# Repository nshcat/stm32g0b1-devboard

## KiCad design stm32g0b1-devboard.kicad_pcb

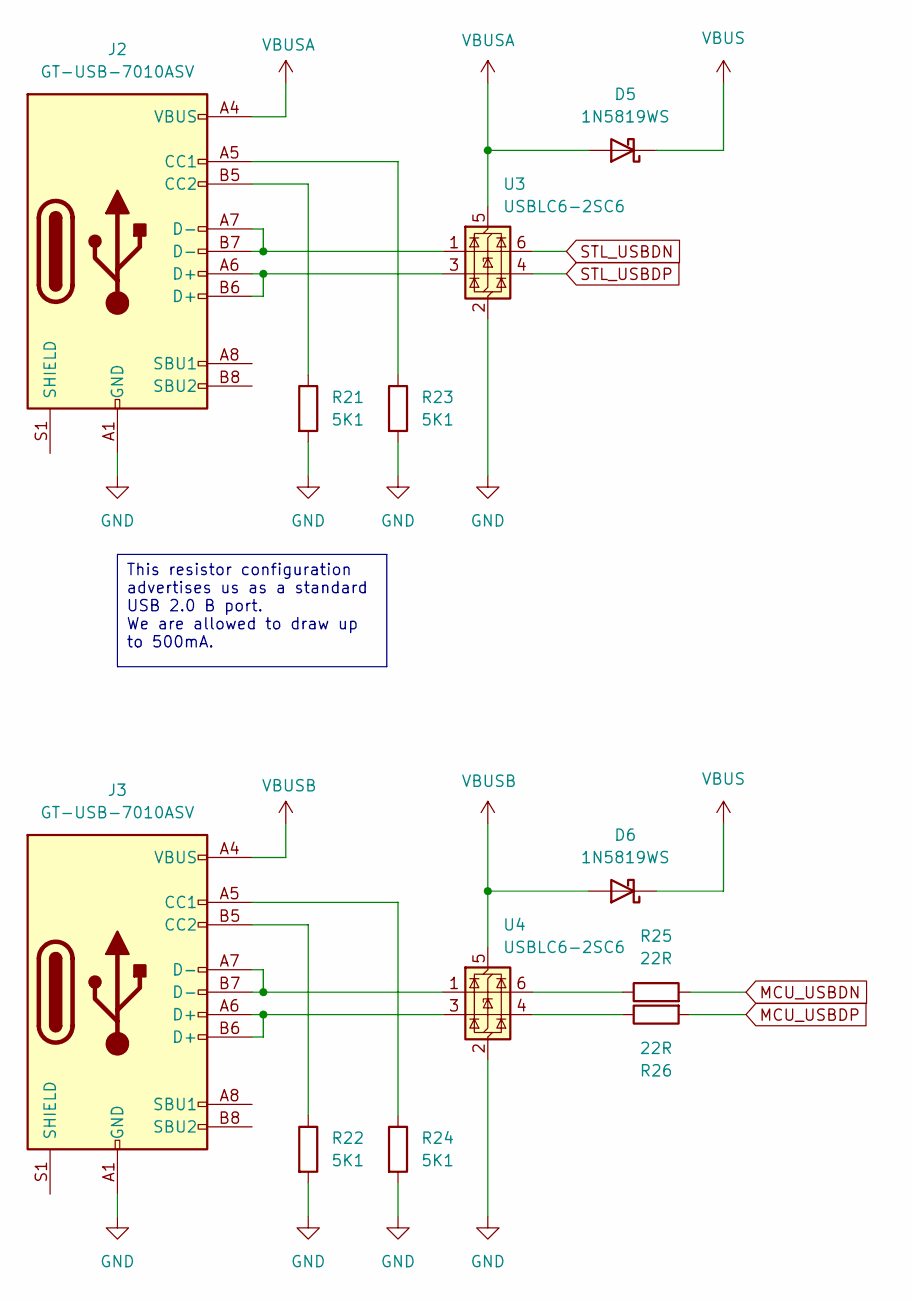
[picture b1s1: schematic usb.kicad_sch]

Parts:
D5, D6: 1N5819WS; D_SOD-323; LCSC Part # C191023
J2, J3: GT-USB-7010ASV; USB_C_Receptacle_G-Switch_GT-USB-7010ASV; LCSC Part # C2988369
R21, R22, R23, R24: 5K1; R_0402_1005Metric; LCSC Part # C25905
R25, R26: 22R; R_0402_1005Metric; LCSC Part # C25092
U3, U4: USBLC6-2SC6; SOT-23-6; LCSC Part # C2687116

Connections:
GND: J2.A1 (GND), J2.A12 (GND), J2.B1 (GND), J2.B12 (GND), J3.A1 (GND), J3.A12 (GND), J3.B1 (GND), J3.B12 (GND), R21.2, R22.2, R23.2, R24.2, U3.2 (GND), U4.2 (GND); also elsewhere on the board
MCU_USBDN: R25.2; also elsewhere on the board
MCU_USBDP: R26.2; also elsewhere on the board
unnamed: J2.A5 (CC1), R23.1
unnamed: J2.B5 (CC2), R21.1
unnamed: J2.A6 (D+), J2.B6 (D+), U3.3 (I/O2)
unnamed: J2.A7 (D-), J2.B7 (D-), U3.1 (I/O1)
unnamed: J3.A5 (CC1), R24.1
unnamed: J3.B5 (CC2), R22.1
unnamed: J3.A6 (D+), J3.B6 (D+), U4.3 (I/O2)
unnamed: J3.A7 (D-), J3.B7 (D-), U4.1 (I/O1)
unnamed: R25.1, U4.6 (I/O1)
unnamed: R26.1, U4.4 (I/O2)
STL_USBDN: U3.6 (I/O1); also elsewhere on the board
STL_USBDP: U3.4 (I/O2); also elsewhere on the board
VBUS: D5.1 (K), D6.1 (K); also elsewhere on the board
VBUSA: D5.2 (A), J2.A4 (VBUS), J2.A9 (VBUS), J2.B4 (VBUS), J2.B9 (VBUS), U3.5 (VBUS)
VBUSB: D6.2 (A), J3.A4 (VBUS), J3.A9 (VBUS), J3.B4 (VBUS), J3.B9 (VBUS), U4.5 (VBUS)

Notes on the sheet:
This resistor configuration advertises us as a standard USB 2.0 B port. We are allowed to draw up to 500mA.

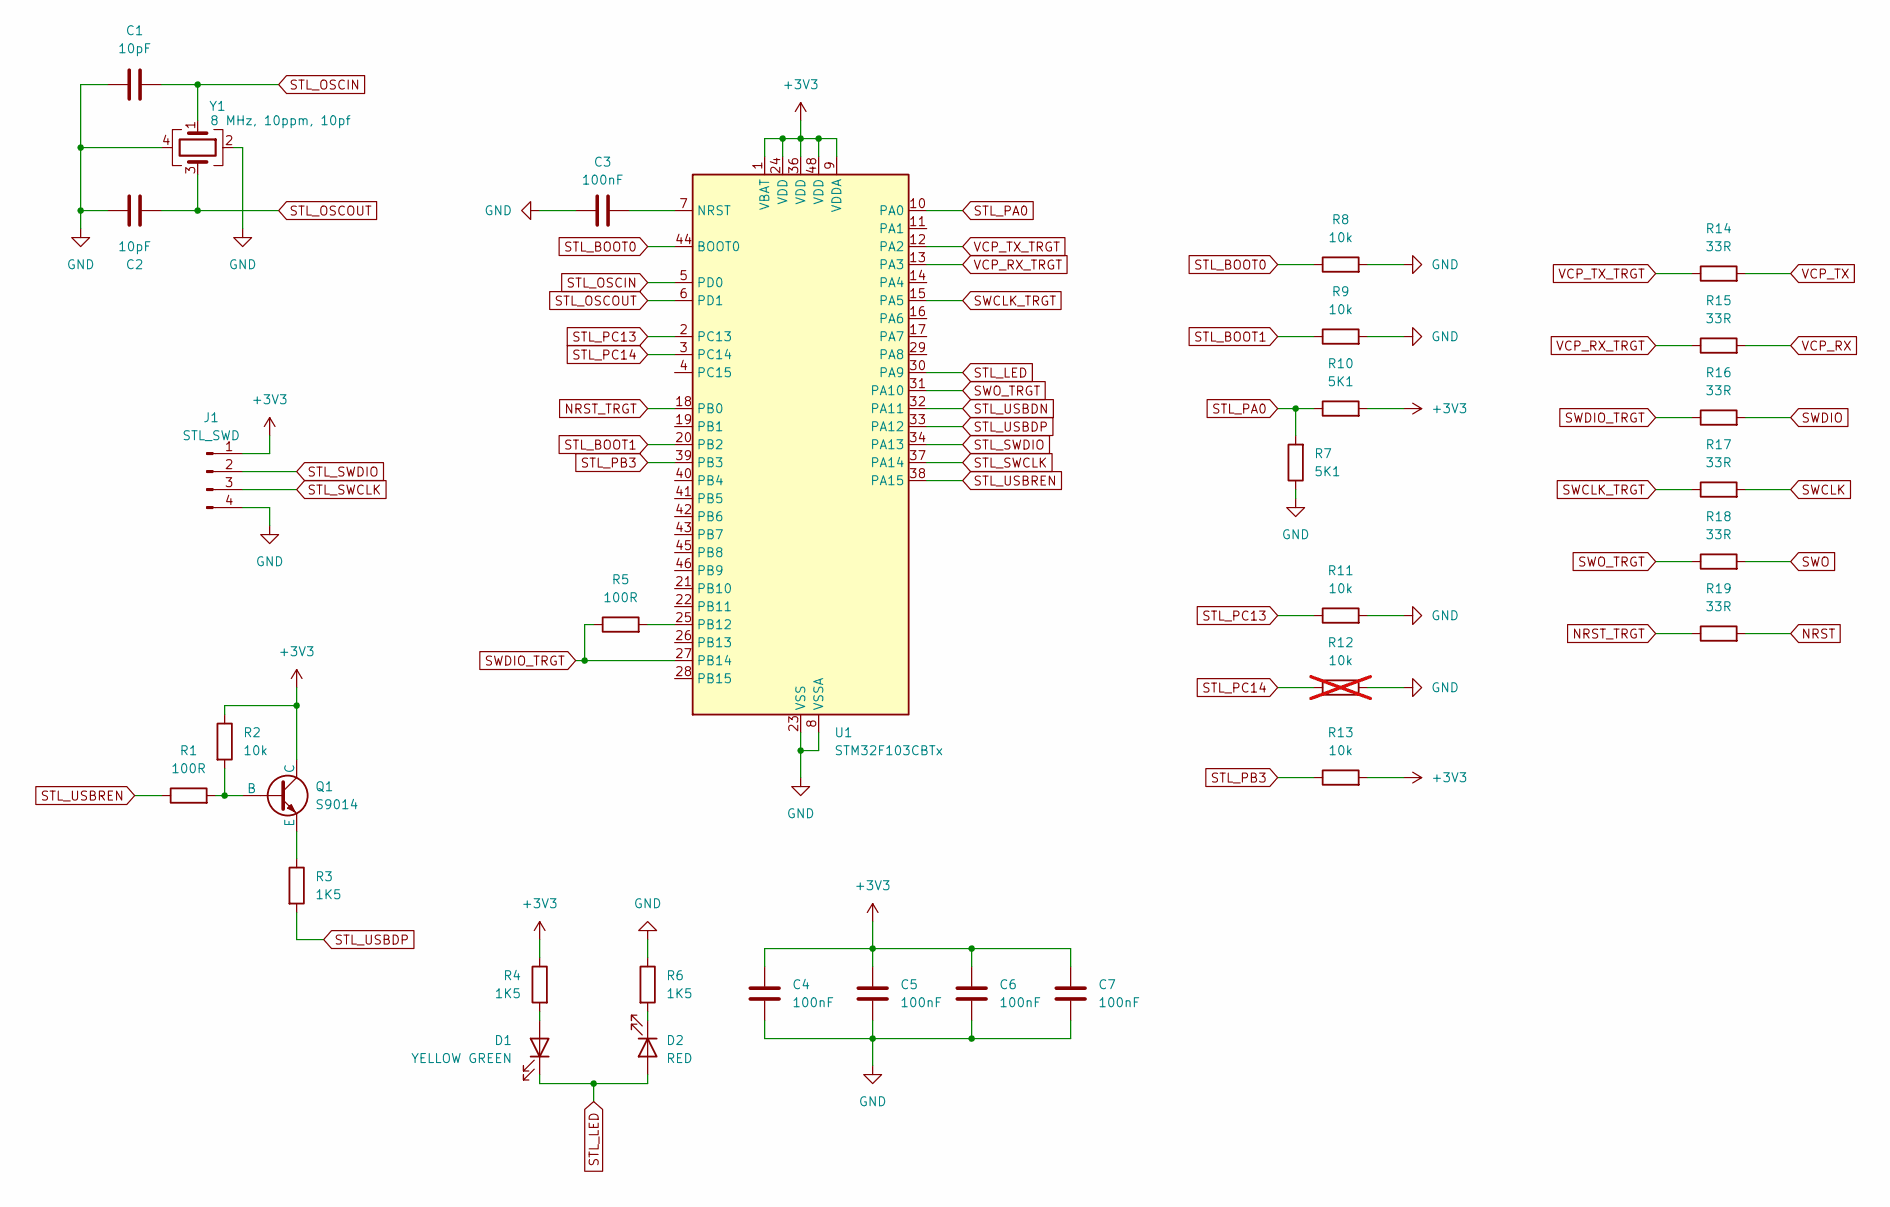
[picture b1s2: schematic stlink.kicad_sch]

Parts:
C1, C2: 10pF; C_0402_1005Metric; LCSC Part # C32949
C3, C4, C5, C6, C7: 100nF; C_0805_2012Metric; LCSC Part # C28233
D1: YELLOW GREEN; LED_0402_1005Metric; LCSC Part # C130722
D2: RED; LED_0402_1005Metric; LCSC Part # C130719
J1: STL_SWD
Q1: S9014; SOT-23; LCSC Part # C20069130
R1, R5: 100R; R_0402_1005Metric; LCSC Part # C106232
R2, R8, R9, R11, R13: 10k; R_0402_1005Metric; LCSC Part # C25744
R3, R4, R6: 1K5; R_0402_1005Metric; LCSC Part # C25867
R7, R10: 5K1; R_0402_1005Metric; LCSC Part # C25905
R12: 10k; R_0402_1005Metric; LCSC Part # C25744; not fitted
R14, R15, R16, R17, R18, R19: 33R; R_0402_1005Metric; LCSC Part # C25105
U1: STM32F103CBTx; LQFP-48_7x7mm_P0.5mm
Y1: 8 MHz, 10ppm, 10pf; Crystal_SMD_3225-4Pin_3.2x2.5mm; LCSC Part # C400090

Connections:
+3V3: C4.2, C5.2, C6.2, C7.2, J1.1, Q1.3 (C), R2.1, R4.1, R10.2, R13.2, U1.1 (VBAT), U1.9 (VDDA), U1.24 (VDD), U1.36 (VDD), U1.48 (VDD); also elsewhere on the board
GND: C1.2, C2.2, C3.2, C4.1, C5.1, C6.1, C7.1, J1.4, R6.1, R7.1, R8.2, R9.2, R11.2, R12.2, U1.8 (VSSA), U1.23 (VSS), U1.35 (VSS), U1.47 (VSS), Y1.2, Y1.4; also elsewhere on the board
NRST: R19.2; also elsewhere on the board
NRST_TRGT: R19.1, U1.18 (PB0)
unnamed: D1.2 (A), R4.2
unnamed: D2.1 (K), R6.2
unnamed: Q1.1 (B), R1.2, R2.2
unnamed: Q1.2 (E), R3.1
unnamed: C3.1, U1.7 (NRST)
unnamed: R5.2, U1.25 (PB12)
STL_BOOT0: R8.1, U1.44 (BOOT0)
STL_BOOT1: R9.1, U1.20 (PB2)
STL_LED: D1.1 (K), D2.2 (A), U1.30 (PA9)
STL_OSCIN: C1.1, U1.5 (PD0), Y1.1
STL_OSCOUT: C2.1, U1.6 (PD1), Y1.3
STL_PA0: R7.2, R10.1, U1.10 (PA0)
STL_PB3: R13.1, U1.39 (PB3)
STL_PC13: R11.1, U1.2 (PC13)
STL_PC14: R12.1, U1.3 (PC14)
STL_SWCLK: J1.3, U1.37 (PA14)
STL_SWDIO: J1.2, U1.34 (PA13)
STL_USBDN: U1.32 (PA11); also elsewhere on the board
STL_USBDP: R3.2, U1.33 (PA12); also elsewhere on the board
STL_USBREN: R1.1, U1.38 (PA15)
SWCLK: R17.2; also elsewhere on the board
SWCLK_TRGT: R17.1, U1.15 (PA5)
SWDIO: R16.2; also elsewhere on the board
SWDIO_TRGT: R5.1, R16.1, U1.27 (PB14)
SWO: R18.2
SWO_TRGT: R18.1, U1.31 (PA10)
VCP_RX: R15.2
VCP_RX_TRGT: R15.1, U1.13 (PA3)
VCP_TX: R14.2
VCP_TX_TRGT: R14.1, U1.12 (PA2)

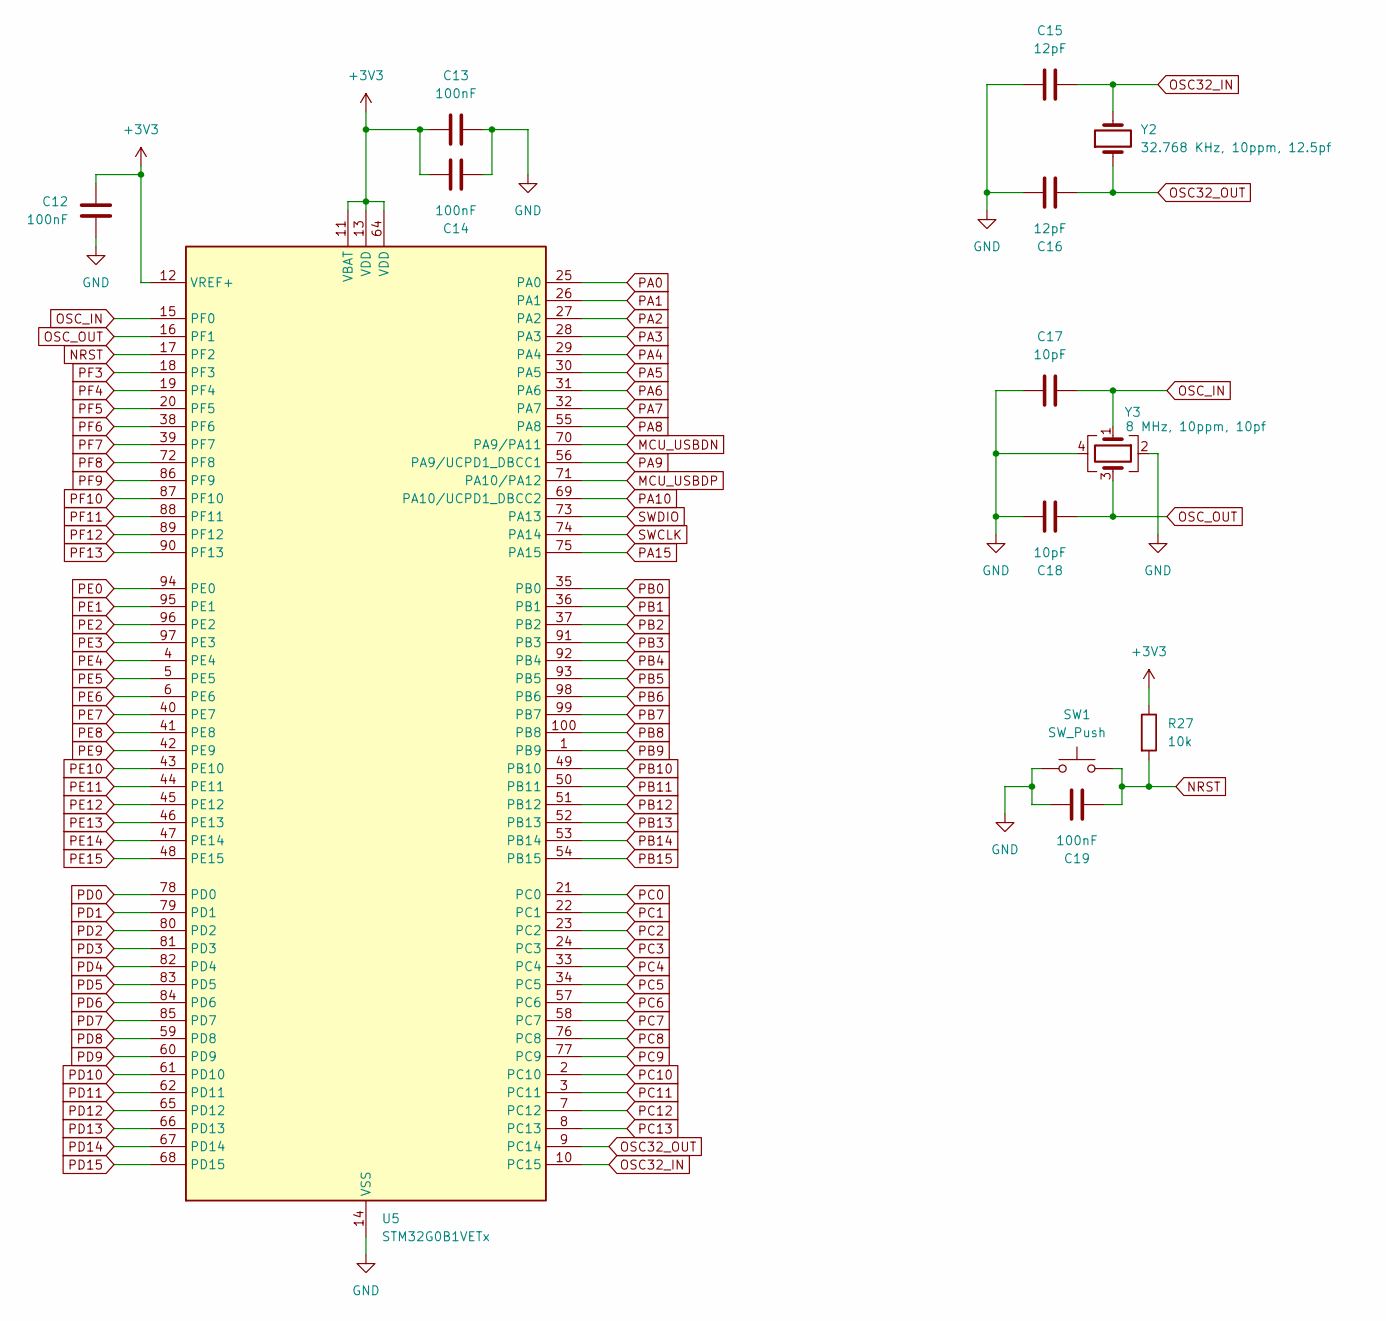
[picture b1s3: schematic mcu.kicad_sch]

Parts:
C12, C13, C14, C19: 100nF; C_0805_2012Metric; LCSC Part # C28233
C15, C16: 12pF; C_0402_1005Metric; LCSC Part # C1547
C17, C18: 10pF; C_0402_1005Metric; LCSC Part # C32949
R27: 10k; R_0402_1005Metric; LCSC Part # C25744
SW1: SW_Push; SW_SPST_B3U-1000P; LCSC Part # C231329
U5: STM32G0B1VETx; LQFP-100_14x14mm_P0.5mm
Y2: 32.768 KHz, 10ppm, 12.5pf; Crystal_SMD_3215-2Pin_3.2x1.5mm; LCSC Part # C32346
Y3: 8 MHz, 10ppm, 10pf; Crystal_SMD_3225-4Pin_3.2x2.5mm; LCSC Part # C400090

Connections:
+3V3: C12.1, C13.1, C14.1, R27.1, U5.11 (VBAT), U5.12 (VREF+), U5.13 (VDD), U5.64 (VDD); also elsewhere on the board
GND: C12.2, C13.2, C14.2, C15.1, C16.2, C17.2, C18.2, C19.1, SW1.1, U5.14 (VSS), U5.63 (VSS), Y3.2, Y3.4; also elsewhere on the board
MCU_USBDN: U5.70 (PA9/PA11); also elsewhere on the board
MCU_USBDP: U5.71 (PA10/PA12); also elsewhere on the board
NRST: C19.2, R27.2, SW1.2, U5.17 (PF2); also elsewhere on the board
OSC32_IN: C15.2, U5.10 (PC15), Y2.2
OSC32_OUT: C16.1, U5.9 (PC14), Y2.1
OSC_IN: C17.1, U5.15 (PF0), Y3.1
OSC_OUT: C18.1, U5.16 (PF1), Y3.3
PA0: U5.25 (PA0); also elsewhere on the board
PA1: U5.26 (PA1); also elsewhere on the board
PA2: U5.27 (PA2); also elsewhere on the board
PA3: U5.28 (PA3); also elsewhere on the board
PA4: U5.29 (PA4); also elsewhere on the board
PA5: U5.30 (PA5); also elsewhere on the board
PA6: U5.31 (PA6); also elsewhere on the board
PA7: U5.32 (PA7); also elsewhere on the board
PA8: U5.55 (PA8); also elsewhere on the board
PA9: U5.56 (PA9/UCPD1_DBCC1); also elsewhere on the board
PA10: U5.69 (PA10/UCPD1_DBCC2); also elsewhere on the board
PA15: U5.75 (PA15); also elsewhere on the board
PB0: U5.35 (PB0); also elsewhere on the board
PB1: U5.36 (PB1); also elsewhere on the board
PB2: U5.37 (PB2); also elsewhere on the board
PB3: U5.91 (PB3); also elsewhere on the board
PB4: U5.92 (PB4); also elsewhere on the board
PB5: U5.93 (PB5); also elsewhere on the board
PB6: U5.98 (PB6); also elsewhere on the board
PB7: U5.99 (PB7); also elsewhere on the board
PB8: U5.100 (PB8); also elsewhere on the board
PB9: U5.1 (PB9); also elsewhere on the board
PB10: U5.49 (PB10); also elsewhere on the board
PB11: U5.50 (PB11); also elsewhere on the board
PB12: U5.51 (PB12); also elsewhere on the board
PB13: U5.52 (PB13); also elsewhere on the board
PB14: U5.53 (PB14); also elsewhere on the board
PB15: U5.54 (PB15); also elsewhere on the board
PC0: U5.21 (PC0); also elsewhere on the board
PC1: U5.22 (PC1); also elsewhere on the board
PC2: U5.23 (PC2); also elsewhere on the board
PC3: U5.24 (PC3); also elsewhere on the board
PC4: U5.33 (PC4); also elsewhere on the board
PC5: U5.34 (PC5); also elsewhere on the board
PC6: U5.57 (PC6); also elsewhere on the board
PC7: U5.58 (PC7); also elsewhere on the board
PC8: U5.76 (PC8); also elsewhere on the board
PC9: U5.77 (PC9); also elsewhere on the board
PC10: U5.2 (PC10); also elsewhere on the board
PC11: U5.3 (PC11); also elsewhere on the board
PC12: U5.7 (PC12); also elsewhere on the board
PC13: U5.8 (PC13); also elsewhere on the board
PD0: U5.78 (PD0); also elsewhere on the board
PD1: U5.79 (PD1); also elsewhere on the board
PD2: U5.80 (PD2); also elsewhere on the board
PD3: U5.81 (PD3); also elsewhere on the board
PD4: U5.82 (PD4); also elsewhere on the board
PD5: U5.83 (PD5); also elsewhere on the board
PD6: U5.84 (PD6); also elsewhere on the board
PD7: U5.85 (PD7); also elsewhere on the board
PD8: U5.59 (PD8); also elsewhere on the board
PD9: U5.60 (PD9); also elsewhere on the board
PD10: U5.61 (PD10); also elsewhere on the board
PD11: U5.62 (PD11); also elsewhere on the board
PD12: U5.65 (PD12); also elsewhere on the board
PD13: U5.66 (PD13); also elsewhere on the board
PD14: U5.67 (PD14); also elsewhere on the board
PD15: U5.68 (PD15); also elsewhere on the board
PE0: U5.94 (PE0); also elsewhere on the board
PE1: U5.95 (PE1); also elsewhere on the board
PE2: U5.96 (PE2); also elsewhere on the board
PE3: U5.97 (PE3); also elsewhere on the board
PE4: U5.4 (PE4); also elsewhere on the board
PE5: U5.5 (PE5); also elsewhere on the board
PE6: U5.6 (PE6); also elsewhere on the board
PE7: U5.40 (PE7); also elsewhere on the board
PE8: U5.41 (PE8); also elsewhere on the board
PE9: U5.42 (PE9); also elsewhere on the board
PE10: U5.43 (PE10); also elsewhere on the board
PE11: U5.44 (PE11); also elsewhere on the board
PE12: U5.45 (PE12); also elsewhere on the board
PE13: U5.46 (PE13); also elsewhere on the board
PE14: U5.47 (PE14); also elsewhere on the board
PE15: U5.48 (PE15); also elsewhere on the board
PF3: U5.18 (PF3); also elsewhere on the board
PF4: U5.19 (PF4); also elsewhere on the board
PF5: U5.20 (PF5); also elsewhere on the board
PF6: U5.38 (PF6); also elsewhere on the board
PF7: U5.39 (PF7); also elsewhere on the board
PF8: U5.72 (PF8); also elsewhere on the board
PF9: U5.86 (PF9); also elsewhere on the board
PF10: U5.87 (PF10); also elsewhere on the board
PF11: U5.88 (PF11); also elsewhere on the board
PF12: U5.89 (PF12); also elsewhere on the board
PF13: U5.90 (PF13); also elsewhere on the board
SWCLK: U5.74 (PA14); also elsewhere on the board
SWDIO: U5.73 (PA13); also elsewhere on the board

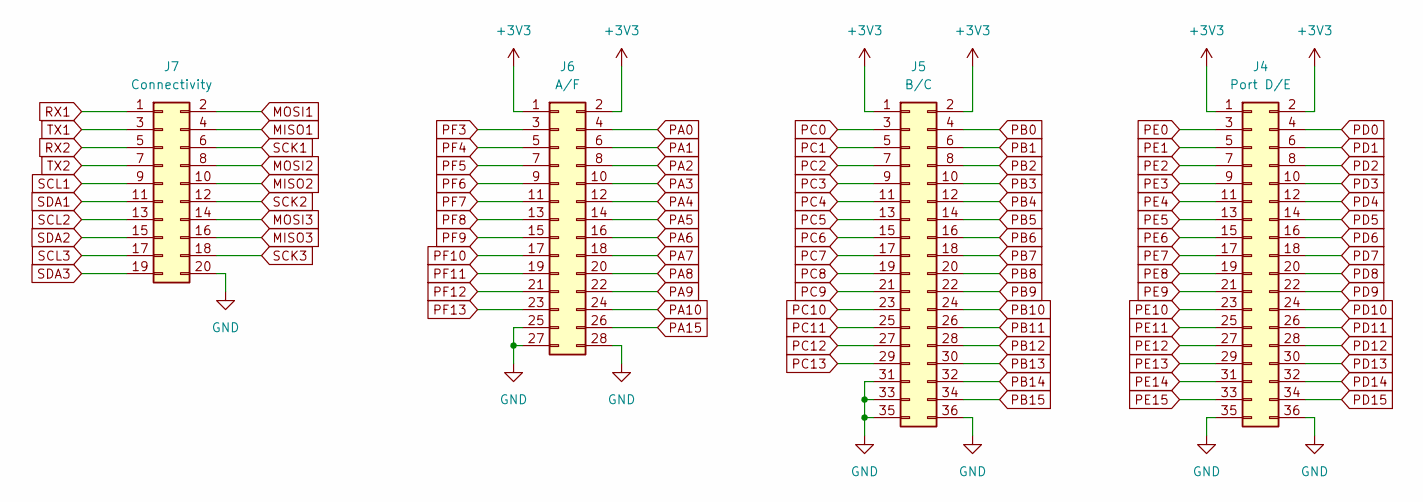
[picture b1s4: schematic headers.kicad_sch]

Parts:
J4: Port D/E; PinSocket_2x18_P2.54mm_Vertical
J5: B/C; PinSocket_2x18_P2.54mm_Vertical
J6: A/F; PinSocket_2x14_P2.54mm_Vertical
J7: Connectivity; PinSocket_2x10_P2.54mm_Vertical

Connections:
+3V3: J4.1, J4.2, J5.1, J5.2, J6.1, J6.2; also elsewhere on the board
GND: J4.35, J4.36, J5.31, J5.33, J5.35, J5.36, J6.25, J6.27, J6.28, J7.20; also elsewhere on the board
MISO1: J7.4
MISO2: J7.10
MISO3: J7.16
MOSI1: J7.2
MOSI2: J7.8
MOSI3: J7.14
PA0: J6.4; also elsewhere on the board
PA1: J6.6; also elsewhere on the board
PA2: J6.8; also elsewhere on the board
PA3: J6.10; also elsewhere on the board
PA4: J6.12; also elsewhere on the board
PA5: J6.14; also elsewhere on the board
PA6: J6.16; also elsewhere on the board
PA7: J6.18; also elsewhere on the board
PA8: J6.20; also elsewhere on the board
PA9: J6.22; also elsewhere on the board
PA10: J6.24; also elsewhere on the board
PA15: J6.26; also elsewhere on the board
PB0: J5.4; also elsewhere on the board
PB1: J5.6; also elsewhere on the board
PB2: J5.8; also elsewhere on the board
PB3: J5.10; also elsewhere on the board
PB4: J5.12; also elsewhere on the board
PB5: J5.14; also elsewhere on the board
PB6: J5.16; also elsewhere on the board
PB7: J5.18; also elsewhere on the board
PB8: J5.20; also elsewhere on the board
PB9: J5.22; also elsewhere on the board
PB10: J5.24; also elsewhere on the board
PB11: J5.26; also elsewhere on the board
PB12: J5.28; also elsewhere on the board
PB13: J5.30; also elsewhere on the board
PB14: J5.32; also elsewhere on the board
PB15: J5.34; also elsewhere on the board
PC0: J5.3; also elsewhere on the board
PC1: J5.5; also elsewhere on the board
PC2: J5.7; also elsewhere on the board
PC3: J5.9; also elsewhere on the board
PC4: J5.11; also elsewhere on the board
PC5: J5.13; also elsewhere on the board
PC6: J5.15; also elsewhere on the board
PC7: J5.17; also elsewhere on the board
PC8: J5.19; also elsewhere on the board
PC9: J5.21; also elsewhere on the board
PC10: J5.23; also elsewhere on the board
PC11: J5.25; also elsewhere on the board
PC12: J5.27; also elsewhere on the board
PC13: J5.29; also elsewhere on the board
PD0: J4.4; also elsewhere on the board
PD1: J4.6; also elsewhere on the board
PD2: J4.8; also elsewhere on the board
PD3: J4.10; also elsewhere on the board
PD4: J4.12; also elsewhere on the board
PD5: J4.14; also elsewhere on the board
PD6: J4.16; also elsewhere on the board
PD7: J4.18; also elsewhere on the board
PD8: J4.20; also elsewhere on the board
PD9: J4.22; also elsewhere on the board
PD10: J4.24; also elsewhere on the board
PD11: J4.26; also elsewhere on the board
PD12: J4.28; also elsewhere on the board
PD13: J4.30; also elsewhere on the board
PD14: J4.32; also elsewhere on the board
PD15: J4.34; also elsewhere on the board
PE0: J4.3; also elsewhere on the board
PE1: J4.5; also elsewhere on the board
PE2: J4.7; also elsewhere on the board
PE3: J4.9; also elsewhere on the board
PE4: J4.11; also elsewhere on the board
PE5: J4.13; also elsewhere on the board
PE6: J4.15; also elsewhere on the board
PE7: J4.17; also elsewhere on the board
PE8: J4.19; also elsewhere on the board
PE9: J4.21; also elsewhere on the board
PE10: J4.23; also elsewhere on the board
PE11: J4.25; also elsewhere on the board
PE12: J4.27; also elsewhere on the board
PE13: J4.29; also elsewhere on the board
PE14: J4.31; also elsewhere on the board
PE15: J4.33; also elsewhere on the board
PF3: J6.3; also elsewhere on the board
PF4: J6.5; also elsewhere on the board
PF5: J6.7; also elsewhere on the board
PF6: J6.9; also elsewhere on the board
PF7: J6.11; also elsewhere on the board
PF8: J6.13; also elsewhere on the board
PF9: J6.15; also elsewhere on the board
PF10: J6.17; also elsewhere on the board
PF11: J6.19; also elsewhere on the board
PF12: J6.21; also elsewhere on the board
PF13: J6.23; also elsewhere on the board
RX1: J7.1
RX2: J7.5
SCK1: J7.6
SCK2: J7.12
SCK3: J7.18
SCL1: J7.9
SCL2: J7.13
SCL3: J7.17
SDA1: J7.11
SDA2: J7.15
SDA3: J7.19
TX1: J7.3
TX2: J7.7

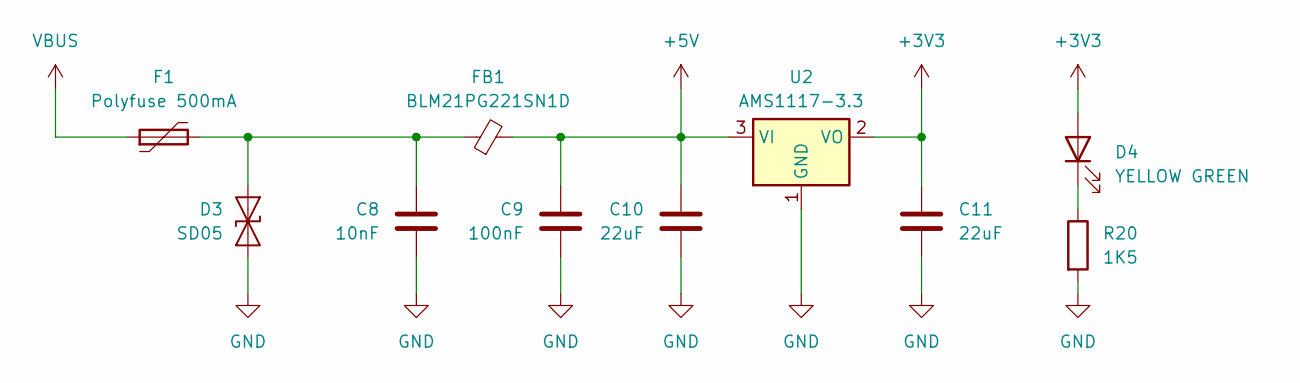
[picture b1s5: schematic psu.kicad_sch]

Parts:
C8: 10nF; C_0805_2012Metric; LCSC Part # C18741
C9: 100nF; C_0805_2012Metric; LCSC Part # C28233
C10, C11: 22uF; C_1206_3216Metric; LCSC Part # C12891
D3: SD05; D_SOD-323; LCSC Part # C118264
D4: YELLOW GREEN; LED_0402_1005Metric; LCSC Part # C130722
F1: Polyfuse 500mA; Fuse_1206_3216Metric; LCSC Part # C369160
FB1: BLM21PG221SN1D; L_0805_2012Metric; LCSC Part # C85840
R20: 1K5; R_0402_1005Metric; LCSC Part # C25867
U2: AMS1117-3.3; SOT-223-3_TabPin2; LCSC Part # C6186

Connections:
+3V3: C11.1, D4.2 (A), U2.2 (VO); also elsewhere on the board
+5V: C9.2, C10.1, FB1.2, U2.3 (VI)
GND: C8.1, C9.1, C10.2, C11.2, D3.2 (A2), R20.2, U2.1 (GND); also elsewhere on the board
unnamed: C8.2, D3.1 (A1), F1.2, FB1.1
unnamed: D4.1 (K), R20.1
VBUS: F1.1; also elsewhere on the board

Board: 4 copper layers, 70 parts (0 on the bottom side), 136 nets, no tracks yet.

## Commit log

2025-07-20 Added gitignore
2025-07-20 Initial commit of project
